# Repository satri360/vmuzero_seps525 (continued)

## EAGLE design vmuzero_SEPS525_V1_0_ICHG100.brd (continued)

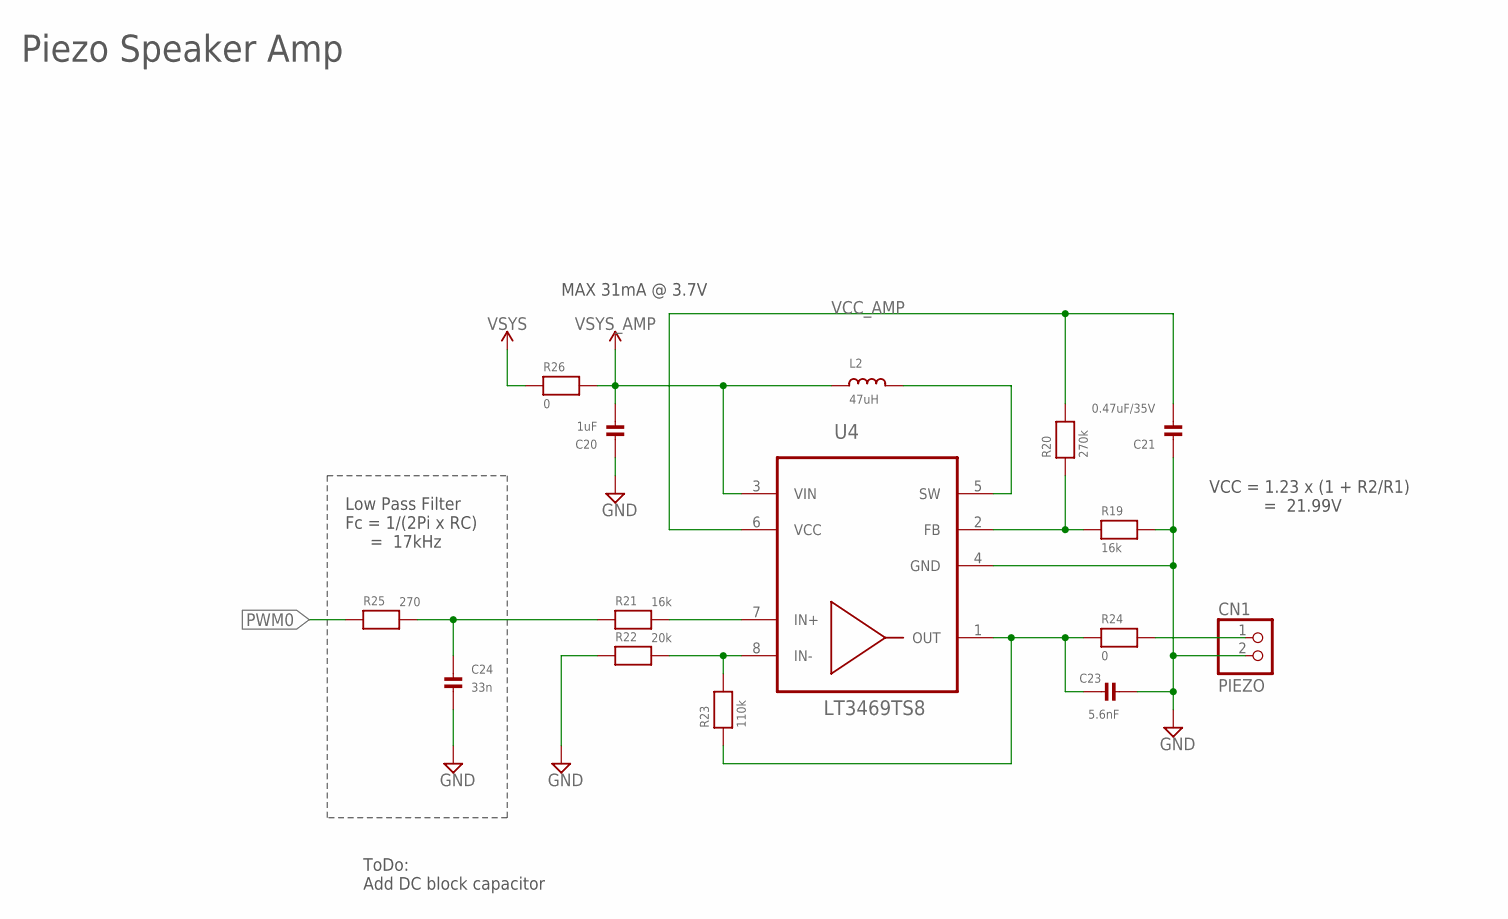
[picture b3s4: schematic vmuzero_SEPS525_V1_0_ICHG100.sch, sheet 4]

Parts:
C20: 1uF; _0805MP
C21: 0.47uF/35V; _0805MP
C23: 5.6nF; _0805MP
C24: 33n; _0805MP
CN1: PIEZO; 1X02_ROUND
L2: 47uH; LQH32C
R19, R21: 16k; _0805MP
R20: 270k; _0805MP
R22: 20k; _0805MP
R23: 110k; _0805MP
R24, R26: 0; _0805MP
R25: 270; _0805MP
U4: LT3469TS8; TSOT-23-8

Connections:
GND: C20.1, C21.1, C23.2, C24.2, CN1.2, R19.2, R22.1, U4.4 (GND); also elsewhere on the board
unnamed: L2.P$2 (2), U4.5 (SW)
unnamed: R19.1, R20.1, U4.2 (FB)
unnamed: C23.1, R23.1, R24.1, U4.1 (OUT)
unnamed: R22.2, R23.2, U4.8 (IN-)
unnamed: CN1.1, R24.2
unnamed: C24.1, R21.1, R25.2
unnamed: R21.2, U4.7 (IN+)
PWM0: R25.1; also elsewhere on the board
VCC_AMP: C21.2, R20.2, U4.6 (VCC)
VSYS: R26.1; also elsewhere on the board
VSYS_AMP: C20.2, L2.P$1 (1), R26.2, U4.3 (VIN)

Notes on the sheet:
Piezo Speaker Amp
Low Pass Filter Fc = 1/(2Pi x RC) = 17kHz
VCC = 1.23 x (1 + R2/R1) = 21.99V
MAX 31mA @ 3.7V
ToDo: Add DC block capacitor

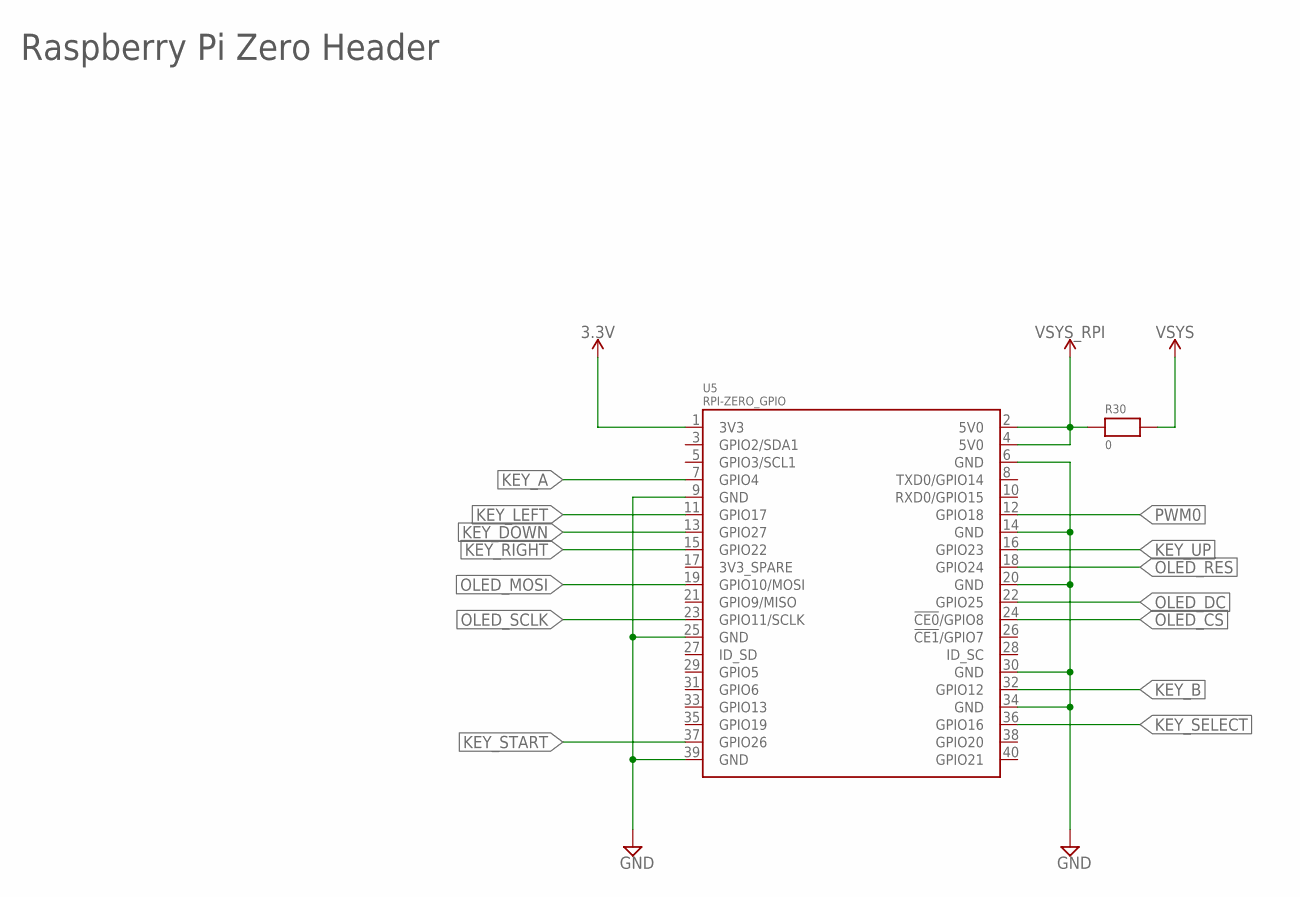
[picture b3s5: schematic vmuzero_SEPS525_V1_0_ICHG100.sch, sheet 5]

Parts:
R30: 0; _0805MP
U5: RPI-ZERO_GPIO; RASP_PI_ZERO_GPIO_SMD

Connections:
3.3V: U5.1 (3V3); also elsewhere on the board
GND: U5.6 (GND), U5.9 (GND), U5.14 (GND), U5.20 (GND), U5.25 (GND), U5.30 (GND), U5.34 (GND), U5.39 (GND); also elsewhere on the board
KEY_A: U5.7 (GPIO4); also elsewhere on the board
KEY_B: U5.32 (GPIO12); also elsewhere on the board
KEY_DOWN: U5.13 (GPIO27); also elsewhere on the board
KEY_LEFT: U5.11 (GPIO17); also elsewhere on the board
KEY_RIGHT: U5.15 (GPIO22); also elsewhere on the board
KEY_SELECT: U5.36 (GPIO16); also elsewhere on the board
KEY_START: U5.37 (GPIO26); also elsewhere on the board
KEY_UP: U5.16 (GPIO23); also elsewhere on the board
OLED_CS: U5.24 (!CE0!/GPIO8); also elsewhere on the board
OLED_DC: U5.22 (GPIO25); also elsewhere on the board
OLED_MOSI: U5.19 (GPIO10/MOSI); also elsewhere on the board
OLED_RES: U5.18 (GPIO24); also elsewhere on the board
OLED_SCLK: U5.23 (GPIO11/SCLK); also elsewhere on the board
PWM0: U5.12 (GPIO18); also elsewhere on the board
VSYS: R30.2; also elsewhere on the board
VSYS_RPI: R30.1, U5.2 (5V0), U5.4 (5V0)

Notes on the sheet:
Raspberry Pi Zero Header

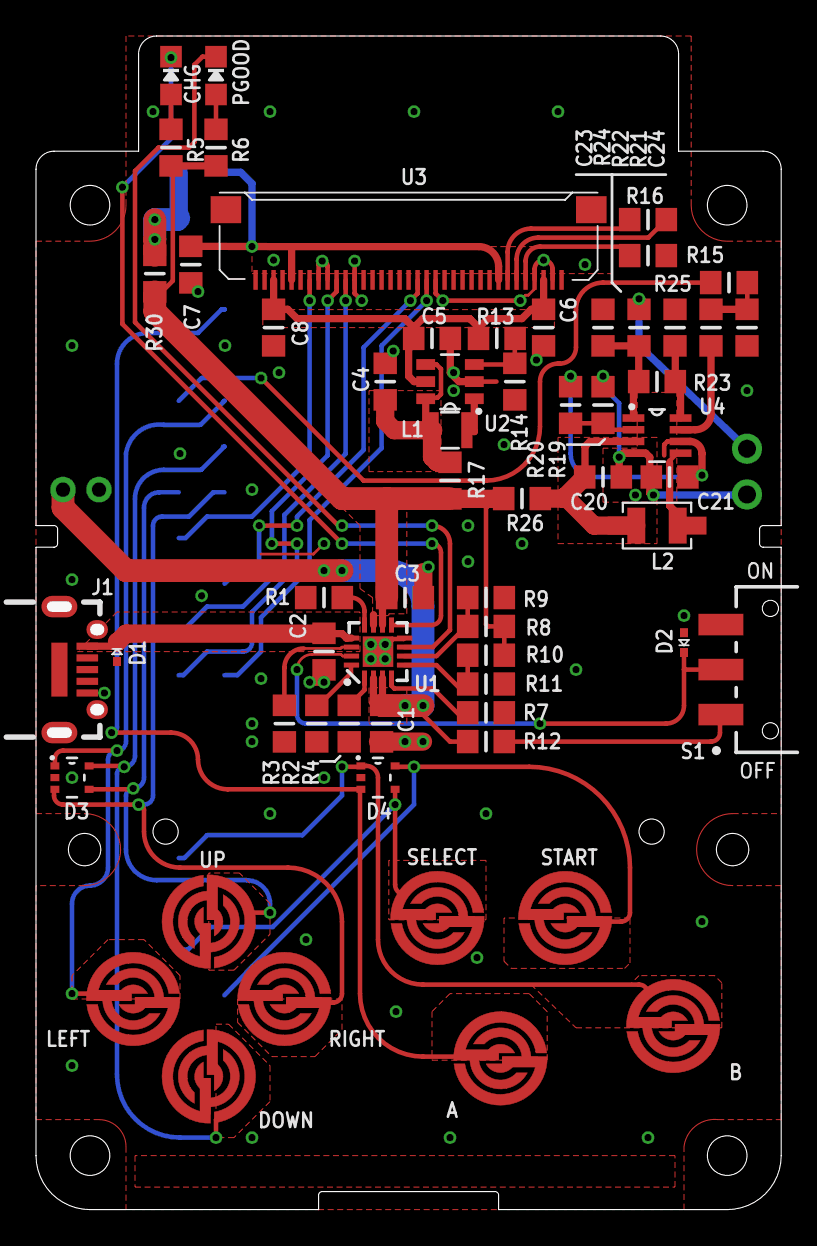
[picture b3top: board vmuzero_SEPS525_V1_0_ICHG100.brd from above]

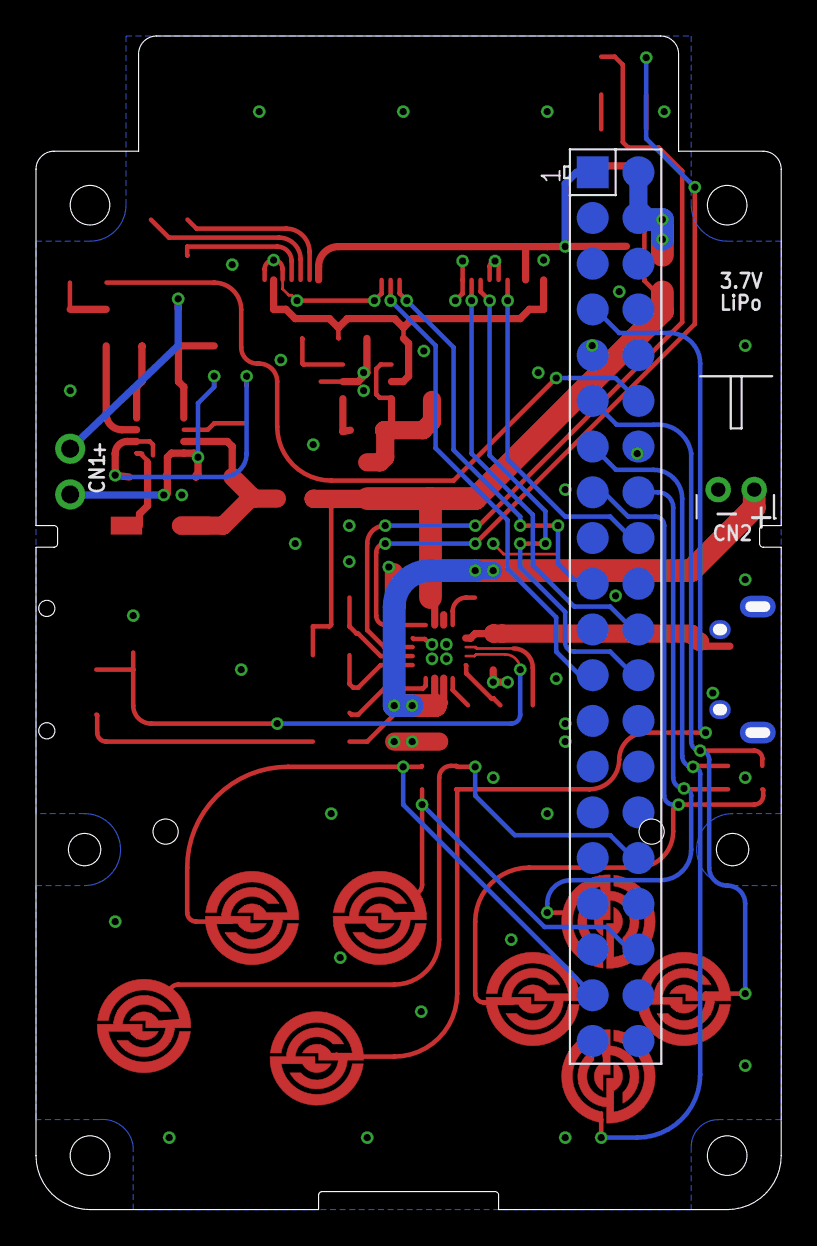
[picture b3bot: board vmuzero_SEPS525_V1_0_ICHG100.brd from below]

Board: 2 copper layers, 41.4 x 65.2 mm, 63 parts (3 on the bottom side), 49 nets.

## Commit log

2018-02-24 Add files via upload
    Changed R6 to 1.5kΩ to reduce brightness of the blue LED
2018-04-02 removed all parts but the keys and ESD
2018-04-02 Added image of board dimensions
2018-04-02 Changed height to 24.5
2018-04-02 Removed unnecessary files
2018-10-07 V2 prototype
2018-11-04 SEPS525 FBTFT Driver for RetroPie-4.3 Kernel 4.9.35+
2018-11-04 SEPS525 FBTFT Driver for RetroPie-4.4 Kernel 4.14.30+
2018-11-05 V2 Released
2019-02-20 Added source file
2019-02-20 SEPS525 FBTFT Driver for RetroPie-4.3 Kernel 4.14.79+
